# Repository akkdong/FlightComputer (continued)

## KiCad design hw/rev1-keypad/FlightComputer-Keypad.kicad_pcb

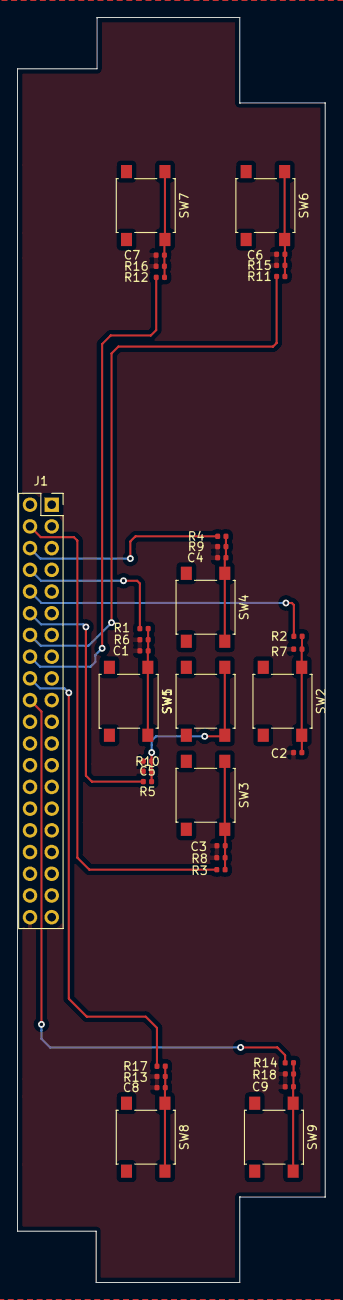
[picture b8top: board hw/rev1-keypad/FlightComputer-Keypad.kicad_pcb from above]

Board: 2 copper layers, 36.0 x 148.0 mm, 37 parts (0 on the bottom side), 20 nets.

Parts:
C1, C2, C3, C4, C5, C6, C7, C8, C9: 0.1uF; C_0402_1005Metric
J1: Conn_02x20_Odd_Even; PinSocket_2x20_P2.54mm_Vertical
R1, R2, R3, R4, R5, R11, R12, R13, R14: 1K; R_0402_1005Metric
R6, R7, R8, R9, R10, R15, R16, R17, R18: 100K; R_0402_1005Metric
SW1, SW2, SW3, SW4, SW5, SW6, SW7, SW8, SW9: SW_Push; SW_SPST_B3S-1000

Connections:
/KEY_DOWN: J1.10, R2.2
/KEY_ENTER: J1.14, R11.2
/KEY_ESCAPE: J1.16, R12.2
/KEY_FUNC1: J1.18, R13.2
/KEY_FUNC2: J1.20, R14.2
/KEY_LEFT: J1.4, R3.2
/KEY_POWER: J1.12, R5.2
/KEY_RIGHT: J1.6, R4.2
/KEY_UP: J1.8, R1.2
GND: C1.2, C2.2, C3.2, C4.2, C5.2, C6.2, C7.2, C8.2, C9.2, J1.40, R6.1, R7.1, R8.1, R9.1, R10.1, R15.1, R16.1, R17.1, R18.1
unnamed: C1.1, R1.1, R6.2, SW1.1
unnamed: C2.1, R2.1, R7.2, SW2.1
unnamed: C3.1, R3.1, R8.2, SW3.1
unnamed: C4.1, R4.1, R9.2, SW4.1
unnamed: C5.1, R5.1, R10.2, SW5.2
unnamed: C6.1, R11.1, R15.2, SW6.1
unnamed: C7.1, R12.1, R16.2, SW7.1
unnamed: C8.1, R13.1, R17.2, SW8.1
unnamed: C9.1, R14.1, R18.2, SW9.1
VCC_PERIH: J1.2, SW1.2, SW2.2, SW3.2, SW4.2, SW5.1, SW6.2, SW7.2, SW8.2, SW9.2

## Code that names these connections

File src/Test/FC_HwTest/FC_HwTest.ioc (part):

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Mcu.Name=STM32H745IITx
Mcu.Package=LQFP176
Mcu.UserName=STM32H745IITx
PA0.GPIOParameters=GPIO_Label,PinAttribute
PA0.GPIO_Label=PWR_WKUP0/KEY_ENTER
PA0.Mode=WakeUp0
PA0.PinAttribute=CortexM7
PA0.Signal=PWR_WKUP0
PA1.ContextOwner=CortexM7
PA1.GPIOParameters=GPIO_Label,PinAttribute
PA1.GPIO_Label=KEY_MENU
PA1.PinAttribute=CortexM7
PA1.Signal=GPIO_Input
PA10.GPIOParameters=GPIO_Label,PinAttribute
PA10.GPIO_Label=DEBUG_RX
PA10.Mode=Asynchronous
PA10.PinAttribute=CortexM7
PA10.Signal=USART1_RX
PA11.GPIOParameters=PinAttribute
PA11.Mode=Device_Only
PA11.PinAttribute=CortexM7
PA11.Signal=USB_OTG_FS_DM
PA12.GPIOParameters=PinAttribute
PA12.Mode=Device_Only
PA12.PinAttribute=CortexM7
PA12.Signal=USB_OTG_FS_DP
PA13\ (JTMS/SWDIO).GPIOParameters=PinAttribute
PA13\ (JTMS/SWDIO).Mode=JTAG_5_pins
PA13\ (JTMS/SWDIO).PinAttribute=CortexM7
PA13\ (JTMS/SWDIO).Signal=DEBUG_JTMS-SWDIO
PA14\ (JTCK/SWCLK).GPIOParameters=PinAttribute
PA14\ (JTCK/SWCLK).Mode=JTAG_5_pins
PA14\ (JTCK/SWCLK).PinAttribute=CortexM7
PA14\ (JTCK/SWCLK).Signal=DEBUG_JTCK-SWCLK
PA15\ (JTDI).GPIOParameters=PinAttribute
PA15\ (JTDI).Mode=JTAG_5_pins
PA15\ (JTDI).PinAttribute=CortexM7
PA15\ (JTDI).Signal=DEBUG_JTDI
PA2.GPIOParameters=GPIO_Label,PinAttribute
PA2.GPIO_Label=GPS_TX
PA2.Mode=Asynchronous
PA2.PinAttribute=CortexM4
PA2.Signal=USART2_TX
PA3.GPIOParameters=GPIO_Label,PinAttribute
PA3.GPIO_Label=GPS_RX
PA3.Mode=Asynchronous
PA3.PinAttribute=CortexM4
PA3.Signal=USART2_RX
PA4.GPIOParameters=GPIO_Label,PinAttribute
PA4.GPIO_Label=EINK_nCS
PA4.Mode=NSS_Signal_Hard_Input
PA4.PinAttribute=CortexM7
PA4.Signal=SPI1_NSS
PA5.GPIOParameters=GPIO_Label,PinAttribute
PA5.GPIO_Label=EINK_SCLK
PA5.Mode=Full_Duplex_Slave
PA5.PinAttribute=CortexM7
PA5.Signal=SPI1_SCK
PA6.GPIOParameters=GPIO_Label,PinAttribute
PA6.GPIO_Label=EINK_MISO
PA6.Mode=Full_Duplex_Slave
PA6.PinAttribute=CortexM7
PA6.Signal=SPI1_MISO
PA7.GPIOParameters=GPIO_Label,PinAttribute
PA7.GPIO_Label=EINK_MOSI
PA7.Mode=Full_Duplex_Slave
PA7.PinAttribute=CortexM7
PA7.Signal=SPI1_MOSI
PA8.ContextOwner=CortexM7
PA8.GPIOParameters=GPIO_Label,PinAttribute
PA8.GPIO_Label=USB_OTG_HS_OVCR
PA8.PinAttribute=CortexM7
PA8.Signal=GPIO_Input
PA9.GPIOParameters=GPIO_Label,PinAttribute
PA9.GPIO_Label=DEBUG_TX
PA9.Mode=Asynchronous
PA9.PinAttribute=CortexM7
PA9.Signal=USART1_TX
PB0.ContextOwner=CortexM4
PB0.GPIOParameters=GPIO_Label,PinAttribute
PB0.GPIO_Label=IMU_DRDY
PB0.PinAttribute=CortexM4
PB0.Signal=GPIO_Input
PB1.ContextOwner=CortexM4
PB1.GPIOParameters=GPIO_Label,PinAttribute
PB1.GPIO_Label=IMU_FSYNC
PB1.PinAttribute=CortexM4
PB1.Signal=GPIO_Input
PB10.GPIOParameters=PinAttribute
PB10.Mode=I2C
PB10.PinAttribute=CortexM4
PB10.Signal=I2C2_SCL
PB11.GPIOParameters=PinAttribute
PB11.Mode=I2C
PB11.PinAttribute=CortexM4
PB11.Signal=I2C2_SDA
PB13.GPIOParameters=PinAttribute
PB13.Mode=Activate_VBUS_FS
PB13.PinAttribute=CortexM7
PB13.Signal=USB_OTG_HS_VBUS
PB14.GPIOParameters=PinAttribute
PB14.Mode=Device_Only_FS
PB14.PinAttribute=CortexM7
PB14.Signal=USB_OTG_HS_DM
PB15.GPIOParameters=PinAttribute
PB15.Mode=Device_Only_FS
PB15.PinAttribute=CortexM7
PB15.Signal=USB_OTG_HS_DP
PB2.ContextOwner=CortexM4
PB2.GPIOParameters=GPIO_Label,PinAttribute
PB2.GPIO_Label=IMU_nINT
PB2.PinAttribute=CortexM4
PB2.Signal=GPIO_Input
PB3\ (JTDO/TRACESWO).GPIOParameters=PinAttribute
PB3\ (JTDO/TRACESWO).Mode=JTAG_5_pins
PB3\ (JTDO/TRACESWO).PinAttribute=CortexM7
PB3\ (JTDO/TRACESWO).Signal=DEBUG_JTDO-SWO
PB4\ (NJTRST).GPIOParameters=PinAttribute
PB4\ (NJTRST).Mode=JTAG_5_pins
PB4\ (NJTRST).PinAttribute=CortexM7
PB4\ (NJTRST).Signal=DEBUG_JTRST
PB5.GPIOParameters=PinAttribute
PB5.Mode=SdramChipSelect2_1
PB5.PinAttribute=CortexM7
PB5.Signal=FMC_SDCKE1
PB6.GPIOParameters=PinAttribute
PB6.Mode=SdramChipSelect2_1
PB6.PinAttribute=CortexM7
PB6.Signal=FMC_SDNE1
PB7.GPIOParameters=PinAttribute
PB7.Mode=I2C
PB7.PinAttribute=CortexM7
PB7.Signal=I2C1_SDA
PB8.GPIOParameters=PinAttribute
PB8.Mode=I2C
PB8.PinAttribute=CortexM7
PB8.Signal=I2C1_SCL
PB9.ContextOwner=CortexM7
PB9.GPIOParameters=GPIO_Label,PinAttribute
PB9.GPIO_Label=PWR_EN_5V
PB9.PinAttribute=CortexM7
PB9.Signal=GPIO_Output
PC0.GPIOParameters=PinAttribute
PC0.PinAttribute=CortexM7
PC0.Signal=FMC_SDNWE
PC1.ContextOwner=CortexM7
PC1.GPIOParameters=GPIO_Label,PinAttribute
PC1.GPIO_Label=LOW_BATTERY
PC1.PinAttribute=CortexM7
PC1.Signal=GPIO_Input
PC10.GPIOParameters=GPIO_Label,PinAttribute
PC10.GPIO_Label=VARIO_TX
PC10.Mode=Asynchronous
PC10.PinAttribute=CortexM4
PC10.Signal=USART3_TX
PC11.GPIOParameters=GPIO_Label,PinAttribute
PC11.GPIO_Label=VARIO_RX
PC11.Mode=Asynchronous
PC11.PinAttribute=CortexM4
PC11.Signal=USART3_RX
PC12.ContextOwner=CortexM7
PC12.GPIOParameters=GPIO_Label,PinAttribute
PC12.GPIO_Label=USB_OTG_FS_VBUS
PC12.PinAttribute=CortexM7
PC12.Signal=GPIO_Input
PC13.ContextOwner=CortexM7
PC13.GPIOParameters=GPIO_Label,PinAttribute
PC13.GPIO_Label=KEY_ESCAPE
PC13.PinAttribute=CortexM7
PC13.Signal=GPIO_Input
PC14-OSC32_IN\ (OSC32_IN).ContextOwner=CortexM7
PC14-OSC32_IN\ (OSC32_IN).GPIOParameters=GPIO_Label,PinAttribute
PC14-OSC32_IN\ (OSC32_IN).GPIO_Label=EINK_CMD
PC14-OSC32_IN\ (OSC32_IN).PinAttribute=CortexM7
PC14-OSC32_IN\ (OSC32_IN).Signal=GPIO_Input
PC15-OSC32_OUT\ (OSC32_OUT).ContextOwner=CortexM7
PC15-OSC32_OUT\ (OSC32_OUT).GPIOParameters=GPIO_Label,PinAttribute
PC15-OSC32_OUT\ (OSC32_OUT).GPIO_Label=EINK_BUSY
PC15-OSC32_OUT\ (OSC32_OUT).PinAttribute=CortexM7
PC15-OSC32_OUT\ (OSC32_OUT).Signal=GPIO_Output
PC3_C.GPIOParameters=PinAttribute
PC3_C.Mode=IN1-Single-Ended
PC3_C.PinAttribute=CortexM4
PC3_C.Signal=ADC3_INP1
PC4.ContextOwner=CortexM7
PC4.GPIOParameters=GPIO_Label,PinAttribute
PC4.GPIO_Label=KEY_LEFT
PC4.PinAttribute=CortexM7
PC4.Signal=GPIO_Input
PC5.ContextOwner=CortexM7
PC5.GPIOParameters=GPIO_Label,PinAttribute
PC5.GPIO_Label=KEY_RIGHT
PC5.PinAttribute=CortexM7
PC5.Signal=GPIO_Input
PC6.ContextOwner=CortexM7
PC6.GPIOParameters=GPIO_Label,PinAttribute
PC6.GPIO_Label=KEY_UP
PC6.PinAttribute=CortexM7
PC6.Signal=GPIO_Input
PC7.ContextOwner=CortexM7
PC7.GPIOParameters=GPIO_Label,PinAttribute
PC7.GPIO_Label=KEY_DOWN
PC7.PinAttribute=CortexM7
PC7.Signal=GPIO_Input
PC8.ContextOwner=CortexM7
PC8.GPIOParameters=GPIO_Label,PinAttribute
PC8.GPIO_Label=KEY_FUNC1
PC8.PinAttribute=CortexM7
PC8.Signal=GPIO_Input
PC9.ContextOwner=CortexM7
PC9.GPIOParameters=GPIO_Label,PinAttribute
PC9.GPIO_Label=KEY_FUNC2
PC9.PinAttribute=CortexM7
PC9.Signal=GPIO_Input
PD0.GPIOParameters=PinAttribute
PD0.PinAttribute=CortexM7
PD0.Signal=FMC_D2_DA2
PD1.GPIOParameters=PinAttribute
PD1.PinAttribute=CortexM7
PD1.Signal=FMC_D3_DA3
PD10.GPIOParameters=PinAttribute
PD10.PinAttribute=CortexM7
PD10.Signal=FMC_D15_DA15
PD11.ContextOwner=CortexM7
PD11.GPIOParameters=GPIO_Label,PinAttribute
PD11.GPIO_Label=EPD_D6
PD11.PinAttribute=CortexM7
PD11.Signal=GPIO_Output
PD12.ContextOwner=CortexM7
PD12.GPIOParameters=GPIO_Label,PinAttribute
PD12.GPIO_Label=EPD_D7
PD12.PinAttribute=CortexM7
PD12.Signal=GPIO_Output
PD13.ContextOwner=CortexM7
PD13.GPIOParameters=GPIO_Label,PinAttribute
PD13.GPIO_Label=USB_OTG_HS_PWR_EN
PD13.PinAttribute=CortexM7
PD13.Signal=GPIO_Output
PD14.GPIOParameters=PinAttribute
PD14.PinAttribute=CortexM7
PD14.Signal=FMC_D0_DA0
PD15.GPIOParameters=PinAttribute
PD15.PinAttribute=CortexM7
PD15.Signal=FMC_D1_DA1
PD2.ContextOwner=CortexM7
PD2.GPIOParameters=GPIO_Label,PinAttribute
PD2.GPIO_Label=EPD_D0
PD2.PinAttribute=CortexM7
PD2.Signal=GPIO_Output
PD3.ContextOwner=CortexM7
PD3.GPIOParameters=GPIO_Label,PinAttribute
PD3.GPIO_Label=EPD_D1
PD3.PinAttribute=CortexM7
PD3.Signal=GPIO_Output
PD4.ContextOwner=CortexM7
PD4.GPIOParameters=GPIO_Label,PinAttribute
PD4.GPIO_Label=EPD_D2
PD4.PinAttribute=CortexM7
PD4.Signal=GPIO_Output
PD5.ContextOwner=CortexM7
PD5.GPIOParameters=GPIO_Label,PinAttribute
PD5.GPIO_Label=EPD_D3
PD5.PinAttribute=CortexM7
PD5.Signal=GPIO_Output
PD6.ContextOwner=CortexM7
PD6.GPIOParameters=GPIO_Label,PinAttribute
PD6.GPIO_Label=EPD_D4
PD6.PinAttribute=CortexM7
PD6.Signal=GPIO_Output
PD7.ContextOwner=CortexM7
PD7.GPIOParameters=GPIO_Label,PinAttribute
PD7.GPIO_Label=EPD_D5
PD7.PinAttribute=CortexM7
PD7.Signal=GPIO_Output
PD8.GPIOParameters=PinAttribute
PD8.PinAttribute=CortexM7
PD8.Signal=FMC_D13_DA13
PD9.GPIOParameters=PinAttribute
PD9.PinAttribute=CortexM7
PD9.Signal=FMC_D14_DA14
PE0.GPIOParameters=PinAttribute
PE0.PinAttribute=CortexM7
PE0.Signal=FMC_NBL0
PE1.GPIOParameters=PinAttribute
PE1.PinAttribute=CortexM7
PE1.Signal=FMC_NBL1
PE10.GPIOParameters=PinAttribute
PE10.PinAttribute=CortexM7
PE10.Signal=FMC_D7_DA7
PE11.GPIOParameters=PinAttribute
PE11.PinAttribute=CortexM7
PE11.Signal=FMC_D8_DA8
PE12.GPIOParameters=PinAttribute
PE12.PinAttribute=CortexM7
PE12.Signal=FMC_D9_DA9
PE13.GPIOParameters=PinAttribute
PE13.PinAttribute=CortexM7
PE13.Signal=FMC_D10_DA10
PE14.GPIOParameters=PinAttribute
PE14.PinAttribute=CortexM7
PE14.Signal=FMC_D11_DA11
PE15.GPIOParameters=PinAttribute
PE15.PinAttribute=CortexM7
PE15.Signal=FMC_D12_DA12
PE2.GPIOParameters=GPIO_Label,PinAttribute
PE2.GPIO_Label=IMU1_SCLK

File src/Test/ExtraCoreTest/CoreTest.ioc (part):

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Mcu.Name=STM32H745XIHx
Mcu.Package=TFBGA240
Mcu.UserName=STM32H745XIHx
PA10.GPIOParameters=PinAttribute
PA10.Mode=Asynchronous
PA10.PinAttribute=CortexM7
PA10.Signal=LPUART1_RX
PA13\ (JTMS/SWDIO).GPIOParameters=PinAttribute
PA13\ (JTMS/SWDIO).Mode=Trace_Asynchronous_SW
PA13\ (JTMS/SWDIO).PinAttribute=CortexM7
PA13\ (JTMS/SWDIO).Signal=DEBUG_JTMS-SWDIO
PA14\ (JTCK/SWCLK).GPIOParameters=PinAttribute
PA14\ (JTCK/SWCLK).Mode=Trace_Asynchronous_SW
PA14\ (JTCK/SWCLK).PinAttribute=CortexM7
PA14\ (JTCK/SWCLK).Signal=DEBUG_JTCK-SWCLK
PA9.GPIOParameters=PinAttribute
PA9.Mode=Asynchronous
PA9.PinAttribute=CortexM7
PA9.Signal=LPUART1_TX
PB0.GPIOParameters=GPIO_Speed,PinAttribute
PB0.GPIO_Speed=GPIO_SPEED_FREQ_HIGH
PB0.PinAttribute=CortexM7
PB0.Signal=S_TIM3_CH3
PB1.GPIOParameters=GPIO_Speed,PinAttribute
PB1.GPIO_Speed=GPIO_SPEED_FREQ_HIGH
PB1.PinAttribute=CortexM7
PB1.Signal=S_TIM3_CH4
PB2.GPIOParameters=GPIO_Speed,PinAttribute
PB2.GPIO_Speed=GPIO_SPEED_FREQ_VERY_HIGH
PB2.Mode=Single Bank 1
PB2.PinAttribute=CortexM7
PB2.Signal=QUADSPI_CLK
PB3\ (JTDO/TRACESWO).GPIOParameters=PinAttribute
PB3\ (JTDO/TRACESWO).Mode=Trace_Asynchronous_SW
PB3\ (JTDO/TRACESWO).PinAttribute=CortexM7
PB3\ (JTDO/TRACESWO).Signal=DEBUG_JTDO-SWO
PB8.GPIOParameters=PinAttribute
PB8.Mode=I2C
PB8.PinAttribute=CortexM7
PB8.Signal=I2C1_SCL
PB9.GPIOParameters=PinAttribute
PB9.Mode=I2C
PB9.PinAttribute=CortexM7
PB9.Signal=I2C1_SDA
PC14-OSC32_IN\ (OSC32_IN).GPIOParameters=PinAttribute
PC14-OSC32_IN\ (OSC32_IN).Mode=LSE-External-Oscillator
PC14-OSC32_IN\ (OSC32_IN).PinAttribute=CortexM7
PC14-OSC32_IN\ (OSC32_IN).Signal=RCC_OSC32_IN
PC15-OSC32_OUT\ (OSC32_OUT).GPIOParameters=PinAttribute
PC15-OSC32_OUT\ (OSC32_OUT).Mode=LSE-External-Oscillator
PC15-OSC32_OUT\ (OSC32_OUT).PinAttribute=CortexM7
PC15-OSC32_OUT\ (OSC32_OUT).Signal=RCC_OSC32_OUT
PC6.GPIOParameters=PinAttribute
PC6.PinAttribute=CortexM7
PC6.Signal=FMC_NWAIT
PD0.GPIOParameters=PinAttribute
PD0.PinAttribute=CortexM7
PD0.Signal=FMC_D2_DA2
PD1.GPIOParameters=PinAttribute
PD1.PinAttribute=CortexM7
PD1.Signal=FMC_D3_DA3
PD10.GPIOParameters=PinAttribute
PD10.PinAttribute=CortexM7
PD10.Signal=FMC_D15_DA15
PD11.GPIOParameters=PinAttribute
PD11.PinAttribute=CortexM7
PD11.Signal=FMC_A16_CLE
PD12.GPIOParameters=PinAttribute
PD12.PinAttribute=CortexM7
PD12.Signal=FMC_A17_ALE
PD13.GPIOParameters=PinAttribute
PD13.PinAttribute=CortexM7
PD13.Signal=FMC_A18
PD14.GPIOParameters=PinAttribute
PD14.PinAttribute=CortexM7
PD14.Signal=FMC_D0_DA0
PD15.GPIOParameters=PinAttribute
PD15.PinAttribute=CortexM7
PD15.Signal=FMC_D1_DA1
PD4.GPIOParameters=PinAttribute
PD4.PinAttribute=CortexM7
PD4.Signal=FMC_NOE
PD5.GPIOParameters=PinAttribute
PD5.PinAttribute=CortexM7
PD5.Signal=FMC_NWE
PD7.GPIOParameters=PinAttribute
PD7.Mode=NorPsramChipSelect1_1
PD7.PinAttribute=CortexM7
PD7.Signal=FMC_NE1
PD8.GPIOParameters=PinAttribute
PD8.PinAttribute=CortexM7
PD8.Signal=FMC_D13_DA13
PD9.GPIOParameters=PinAttribute
PD9.PinAttribute=CortexM7
PD9.Signal=FMC_D14_DA14
PE0.GPIOParameters=PinAttribute
PE0.PinAttribute=CortexM7
PE0.Signal=FMC_NBL0
PE1.GPIOParameters=PinAttribute
PE1.PinAttribute=CortexM7
PE1.Signal=FMC_NBL1
PE10.GPIOParameters=PinAttribute
PE10.PinAttribute=CortexM7
PE10.Signal=FMC_D7_DA7
PE11.GPIOParameters=PinAttribute
PE11.PinAttribute=CortexM7
PE11.Signal=FMC_D8_DA8
PE12.GPIOParameters=PinAttribute
PE12.PinAttribute=CortexM7
PE12.Signal=FMC_D9_DA9
PE13.GPIOParameters=PinAttribute
PE13.PinAttribute=CortexM7
PE13.Signal=FMC_D10_DA10
PE14.GPIOParameters=PinAttribute
PE14.PinAttribute=CortexM7
PE14.Signal=FMC_D11_DA11
PE15.GPIOParameters=PinAttribute
PE15.PinAttribute=CortexM7
PE15.Signal=FMC_D12_DA12
PE2.GPIOParameters=PinAttribute
PE2.PinAttribute=CortexM7
PE2.Signal=FMC_A23
PE3.GPIOParameters=PinAttribute
PE3.PinAttribute=CortexM7
PE3.Signal=FMC_A19
PE4.GPIOParameters=PinAttribute
PE4.PinAttribute=CortexM7
PE4.Signal=FMC_A20
PE5.GPIOParameters=PinAttribute
PE5.PinAttribute=CortexM7
PE5.Signal=FMC_A21
PE6.GPIOParameters=PinAttribute
PE6.PinAttribute=CortexM7
PE6.Signal=FMC_A22
PE7.GPIOParameters=PinAttribute
PE7.PinAttribute=CortexM7
PE7.Signal=FMC_D4_DA4
PE8.GPIOParameters=PinAttribute
PE8.PinAttribute=CortexM7
PE8.Signal=FMC_D5_DA5
PE9.GPIOParameters=PinAttribute
PE9.PinAttribute=CortexM7
PE9.Signal=FMC_D6_DA6
PF0.GPIOParameters=PinAttribute
PF0.PinAttribute=CortexM7
PF0.Signal=FMC_A0
PF1.GPIOParameters=PinAttribute
PF1.PinAttribute=CortexM7
PF1.Signal=FMC_A1
PF10.ContextOwner=CortexM7
PF10.GPIOParameters=GPIO_Label,PinAttribute
PF10.GPIO_Label=LCD_BL
PF10.PinAttribute=CortexM7
PF10.Signal=GPIO_Output
PF11.GPIOParameters=PinAttribute
PF11.PinAttribute=CortexM7
PF11.Signal=FMC_SDNRAS
PF12.GPIOParameters=PinAttribute
PF12.PinAttribute=CortexM7
PF12.Signal=FMC_A6
PF13.GPIOParameters=PinAttribute
PF13.PinAttribute=CortexM7
PF13.Signal=FMC_A7
PF14.GPIOParameters=PinAttribute
PF14.PinAttribute=CortexM7
PF14.Signal=FMC_A8
PF15.GPIOParameters=PinAttribute
PF15.PinAttribute=CortexM7
PF15.Signal=FMC_A9
PF2.GPIOParameters=PinAttribute
PF2.PinAttribute=CortexM7
PF2.Signal=FMC_A2
PF3.GPIOParameters=PinAttribute
PF3.PinAttribute=CortexM7
PF3.Signal=FMC_A3
PF4.GPIOParameters=PinAttribute
PF4.PinAttribute=CortexM7
PF4.Signal=FMC_A4
PF5.GPIOParameters=PinAttribute
PF5.PinAttribute=CortexM7
PF5.Signal=FMC_A5
PF6.GPIOParameters=GPIO_Speed,PinAttribute
PF6.GPIO_Speed=GPIO_SPEED_FREQ_VERY_HIGH
PF6.Mode=Single Bank 1
PF6.PinAttribute=CortexM7
PF6.Signal=QUADSPI_BK1_IO3
PF7.GPIOParameters=GPIO_Speed,PinAttribute
PF7.GPIO_Speed=GPIO_SPEED_FREQ_VERY_HIGH
PF7.Mode=Single Bank 1
PF7.PinAttribute=CortexM7
PF7.Signal=QUADSPI_BK1_IO2
PF8.GPIOParameters=GPIO_Speed,PinAttribute
PF8.GPIO_Speed=GPIO_SPEED_FREQ_VERY_HIGH
PF8.Mode=Single Bank 1
PF8.PinAttribute=CortexM7
PF8.Signal=QUADSPI_BK1_IO0
PF9.GPIOParameters=GPIO_Speed,PinAttribute
PF9.GPIO_Speed=GPIO_SPEED_FREQ_VERY_HIGH
PF9.Mode=Single Bank 1
PF9.PinAttribute=CortexM7
PF9.Signal=QUADSPI_BK1_IO1
PG0.GPIOParameters=PinAttribute
PG0.PinAttribute=CortexM7
PG0.Signal=FMC_A10
PG1.GPIOParameters=PinAttribute
PG1.PinAttribute=CortexM7
PG1.Signal=FMC_A11
PG10.ContextOwner=CortexM7
PG10.GPIOParameters=GPIO_Label,PinAttribute
PG10.GPIO_Label=LED1
PG10.PinAttribute=CortexM7
PG10.Signal=GPIO_Output
PG15.GPIOParameters=PinAttribute
PG15.PinAttribute=CortexM7
PG15.Signal=FMC_SDNCAS
PG2.GPIOParameters=PinAttribute
PG2.PinAttribute=CortexM7
PG2.Signal=FMC_A12
PG3.GPIOParameters=PinAttribute
PG3.PinAttribute=CortexM7
PG3.Signal=FMC_A13
PG4.GPIOParameters=PinAttribute
PG4.PinAttribute=CortexM7
PG4.Signal=FMC_A14_BA0
PG5.GPIOParameters=PinAttribute
PG5.PinAttribute=CortexM7
PG5.Signal=FMC_A15_BA1
PG6.GPIOParameters=GPIO_Speed,PinAttribute
PG6.GPIO_Speed=GPIO_SPEED_FREQ_VERY_HIGH
PG6.Mode=Single Bank 1
PG6.PinAttribute=CortexM7
PG6.Signal=QUADSPI_BK1_NCS
PG8.GPIOParameters=PinAttribute
PG8.PinAttribute=CortexM7
PG8.Signal=FMC_SDCLK
PH0-OSC_IN\ (PH0).GPIOParameters=PinAttribute
PH0-OSC_IN\ (PH0).Mode=HSE-External-Oscillator
PH0-OSC_IN\ (PH0).PinAttribute=CortexM7
PH0-OSC_IN\ (PH0).Signal=RCC_OSC_IN
PH1-OSC_OUT\ (PH1).GPIOParameters=PinAttribute
PH1-OSC_OUT\ (PH1).Mode=HSE-External-Oscillator
PH1-OSC_OUT\ (PH1).PinAttribute=CortexM7
PH1-OSC_OUT\ (PH1).Signal=RCC_OSC_OUT
PH10.GPIOParameters=PinAttribute
PH10.PinAttribute=CortexM7
PH10.Signal=FMC_D18
PH11.GPIOParameters=PinAttribute
PH11.PinAttribute=CortexM7
PH11.Signal=FMC_D19
PH12.GPIOParameters=PinAttribute
PH12.PinAttribute=CortexM7
PH12.Signal=FMC_D20
PH13.GPIOParameters=PinAttribute
PH13.PinAttribute=CortexM7
PH13.Signal=FMC_D21
PH14.GPIOParameters=PinAttribute
PH14.PinAttribute=CortexM7
PH14.Signal=FMC_D22
PH15.GPIOParameters=PinAttribute
PH15.PinAttribute=CortexM7
PH15.Signal=FMC_D23
PH5.GPIOParameters=PinAttribute
PH5.PinAttribute=CortexM7
PH5.Signal=FMC_SDNWE
PH6.GPIOParameters=PinAttribute
PH6.Mode=SdramChipSelect2_1
PH6.PinAttribute=CortexM7
PH6.Signal=FMC_SDNE1
PH7.GPIOParameters=PinAttribute
PH7.Mode=SdramChipSelect2_1
PH7.PinAttribute=CortexM7
PH7.Signal=FMC_SDCKE1
PH8.GPIOParameters=PinAttribute
PH8.PinAttribute=CortexM7
PH8.Signal=FMC_D16
PH9.GPIOParameters=PinAttribute
PH9.PinAttribute=CortexM7
PH9.Signal=FMC_D17
PI0.GPIOParameters=PinAttribute
PI0.PinAttribute=CortexM7
PI0.Signal=FMC_D24
PI1.GPIOParameters=PinAttribute
PI1.PinAttribute=CortexM7
PI1.Signal=FMC_D25
PI10.GPIOParameters=PinAttribute
PI10.PinAttribute=CortexM7
PI10.Signal=FMC_D31
PI11.GPIOParameters=PinAttribute
PI11.Mode=RGB666
PI11.PinAttribute=CortexM7
PI11.Signal=LTDC_G6
PI12.GPIOParameters=PinAttribute
PI12.Mode=RGB666
PI12.PinAttribute=CortexM7
PI12.Signal=LTDC_HSYNC
PI13.GPIOParameters=PinAttribute
PI13.Mode=RGB666
PI13.PinAttribute=CortexM7
PI13.Signal=LTDC_VSYNC
PI14.GPIOParameters=PinAttribute
PI14.Mode=RGB666
PI14.PinAttribute=CortexM7
PI14.Signal=LTDC_CLK
PI2.GPIOParameters=PinAttribute
PI2.PinAttribute=CortexM7
PI2.Signal=FMC_D26
PI3.GPIOParameters=PinAttribute
PI3.PinAttribute=CortexM7
PI3.Signal=FMC_D27
PI4.GPIOParameters=PinAttribute
PI4.PinAttribute=CortexM7
PI4.Signal=FMC_NBL2

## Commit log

2018-10-31 test...
2018-11-13 test widget drawing
2018-11-15 test
2018-11-16 ref-module : GxEPD
2018-11-21 architecture draft
2018-11-22 test standby-mode
2018-11-22 update document
2019-01-31 test: sine-wave generator --> for esp32
2019-04-01 update sinewave
2020-08-07 pcb working...
2020-08-07 add submoules: libvncserver, PaperTTY
2020-08-08 VncClient test program
2020-08-09 VNCClient test : TBD
2020-08-12 schematic working...
2020-08-13 add 5in HDMI LCD datasheet
2020-08-14 add raspberry pi zero pinout
2020-08-28 RPI ZH851 Touch test
2020-08-28 rpi-touch working
2020-08-29 rpi-touch working...
2020-08-30 add reference git
2020-09-03 fw v1.21 -> v1.25
2020-09-14 references
2020-09-15 add missing schematic
2020-09-24 add stm32h745 pinout
2020-09-25 ignore .sch-bak, .bck
2020-09-25 schematic working....
2020-10-03 update pin-map bom working... case working...
2020-10-04 update pinmap
2020-10-05 cube-mx examples
2020-10-10 add missing files
2020-10-10 add keypad pcb & share library
2020-10-12 change folder tree
2020-10-16 pcb dimension
2020-10-24 pcb complete 1st
2020-11-03 gerber
2020-11-04 gerber final
2020-11-08 changed min via-size: 0.4 -> 0.45
2020-11-09 trace length matching & generate gerber files
2020-11-09 stm32cubemx configuration
2020-11-13 schematic pdf files
2020-11-17 reconf mcu
2020-11-18 firmware base
2020-11-23 test H/W cont...
2020-11-23 add H/W test project
2020-11-23 fixed eink position
2020-11-23 TEST SDRAM
2020-11-23 remove debug-hex
2020-11-24 test sdram(ok), quad-spi-nor(cond)
2020-11-24 some pictures
2020-11-25 h/w test GPS: OK NOR-FLASH: Direct(OK), MemoryMapped(FAIL: NEED MORE TIME) IMU(SPI): H/W Fault -> swapped Pin 3,4 PMIC: Communication(OK), Turn on Power Rail(FAIL)
2020-11-25 stm32 usb documents
2020-11-26 h/w test cont - spi1: ok - uart3: ok - spi4: communication ok. but device does not response properly
2020-11-26 H/W test : USB-HS-MSC -> SDRAM as Disk
2020-11-26 H/W Test: change imu interface (SPI -> I2C)
2020-11-27 H/W test: NOR TO MSC
2020-11-30 deep-sleep test (cont)
2020-11-30 replace pmic parts
2020-12-02 air-speed
2020-12-03 fixing pcb layout (cont)
2020-12-04 reinforce PMIC layout
2020-12-04 add missing footprints
2020-12-04 change 5v booster --> TPS61022
2020-12-05 rework pcb design
2020-12-06 update current sensor
2020-12-07 PIMIC rework finished
2020-12-07 rename to Current sensor
2020-12-08 booster
2020-12-09 USB Host Test(cont)
2020-12-09 update extra purchase
2020-12-11 H/W Test: HID Host
2020-12-11 ioc modified
2020-12-18 add documents
2020-12-22 remove SystemWorkbench
2020-12-27 removed FC_HWTest added FC_Test
2020-12-28 test code
2020-12-29 BSP: qspi
2020-12-29 QSPI External Loader
2020-12-29 add empty folder
2020-12-30 test usb/fatfs (TBD)
2020-12-30 USB_HS(MSC), USB_FS(CDC) TBD...
2020-12-30 link by relative path
2020-12-30 FATFS Test (TBD)
2020-12-31 TEST TBD
2021-01-02 peripheral initialization
2021-01-02 test code: dir
2021-01-02 fixed memory-mapped mode (dummy cycle)
2021-01-05 External EINK PMIC
2021-01-10 EINK Test (OK)
2021-01-11 mono test (TBD)
2021-01-12 epd partial update (TBD)
2021-01-13 fast fast
2021-01-15 another waveform
2021-01-20 add tensorflow lite for microcontroller example
2021-01-22 pcb rev2 (TBD)
2021-01-23 FC rev2
2021-01-24 change board outline
2021-01-24 fixed incorrect connection
2021-01-25 FC first
2021-01-25 LT1945 voltage calculator
2021-01-25 ml test
2021-01-26 change fc configuration
2021-01-26 HID host library
2021-01-26 add drivers & middlewares
2021-01-27 usb device/host
2021-01-27 bat_sense add capacitor
2021-01-28 Arduino porting (TBD)
2021-01-31 add missing file
2021-01-31 use callback
2021-02-01 epd protocol (TBD)
2021-02-19 framebuffer outline
2021-02-20 buzzer (TBD)
2021-02-26 rev2
2021-02-26 re-numbering
2021-03-01 on/off vcom
2021-03-01 add missing library
2021-03-16 mod BOM
2021-04-22 PMIC driver (TBD)
2021-04-22 PMIC test (done)
2021-04-30 another vario: AcousticVario
2021-05-07 case mod
2021-05-14 case bottom/spacer stl
2021-05-15 fixed bottom case re-design spacer
2021-05-27 update cover, enclosure
2021-05-28 usb power-delivery stubs
2021-06-04 case
2021-06-09 redraw waveform
2021-06-14 add lvgl gitmodule
2021-06-14 lvgl porting (TBD)
2021-06-18 lvgl basic porting
2021-11-05 fixed miss connection
2021-11-12 test: airspeed
2021-11-12 fixed build error
2021-11-16 show raw pressure data
2021-11-16 fixed calculation error
2021-11-16 ms4625 valid ranged : 10~80 or 10~90% ?
2021-11-18 another display logic(InkPlate) - working...
2021-11-21 EPD Display (working)
2021-11-23 keypad
2021-11-23 add adafruit_gfx
2021-11-24 partial update (working)
2021-11-24 fastUpdate
2021-11-24 add document
2021-11-25 build cm4
2021-11-28 inter-process communication (working)
2021-12-06 shell template
2021-12-06 extra core-board
2021-12-07 sdram test (failed!)
2021-12-22 GY-91 test
2021-12-22 timer test
2021-12-23 sine-wave generation
2021-12-24 beep-sound test
2021-12-25 shell command & stand-by
2021-12-26 standby
2021-12-26 arduino code: current measurement
2021-12-29 replace arduino code with latest (not working)
2021-12-29 fixed running error
2021-12-31 - sensor & variometer library - update SPI, Wire library
2021-12-31 shared memory map, debug, ...
2022-01-01 fixed standby error
2022-01-01 optimize voltage reading
2022-01-01 current-sensor zero calibration
2022-01-02 display sensor info
2022-01-02 gps debugging
2022-01-11 update whole line
2022-01-13 extra-test: lcd
2022-01-19 epd-pmic test (tbd)
